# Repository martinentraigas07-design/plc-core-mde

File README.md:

# plc-core-mde
Open modular PLC based on ESP32 with web interface, IEC61131 FBD programming, RS485 Modbus expansion and cloud simulator support
# PLC-CORE-MDE

PLC-CORE-MDE is an open, modular and scalable programmable logic controller (PLC) based on ESP32, designed for education, automation, industrial control and experimental development.

The project is focused on creating a flexible, low-cost and high-performance control platform that can be expanded using external modules connected through RS485 Modbus communication.

The system includes an embedded web server that allows configuration, monitoring and programming directly from a web browser without the need for additional software.

Main features:

- ESP32 based core module
- Embedded web server
- Graphical programming using FBD (Function Block Diagram)
- IEC 61131 inspired runtime
- RS485 Modbus expansion modules
- Automatic module detection
- Digital and analog IO support
- PWM outputs
- Timers, counters and memory blocks
- Modular hardware for DIN rail mounting
- Educational oriented design
- Open architecture
- Cloud simulator support (future)
- Virtual PLC for training and testing

Architecture:

CORE module:
- Processing
- Web server
- Runtime
- Communication

Expansion modules:
- Digital inputs
- Digital outputs
- Analog inputs
- Analog outputs
- Mixed IO
- Modbus devices

Future features:

- Cloud PLC simulator
- USB communication mode
- Modbus remote mode
- Gateway mode
- Ethernet / TCP mode
- Hybrid simulation + real PLC

This project is intended for:

- Technical education
- Industrial automation learning
- Experimental development
- Custom control systems
- Low-cost PLC applications

Author: Martin Entraigas
Project: PLC-CORE-MDE

## License

PLC-CORE-MDE License v1.0

Copyright (c) 2026 Martín Entraigas / PLC-CORE-MDE, Argentina

Educational use allowed.
Commercial use requires authorization.

See LICENSE file for full terms.

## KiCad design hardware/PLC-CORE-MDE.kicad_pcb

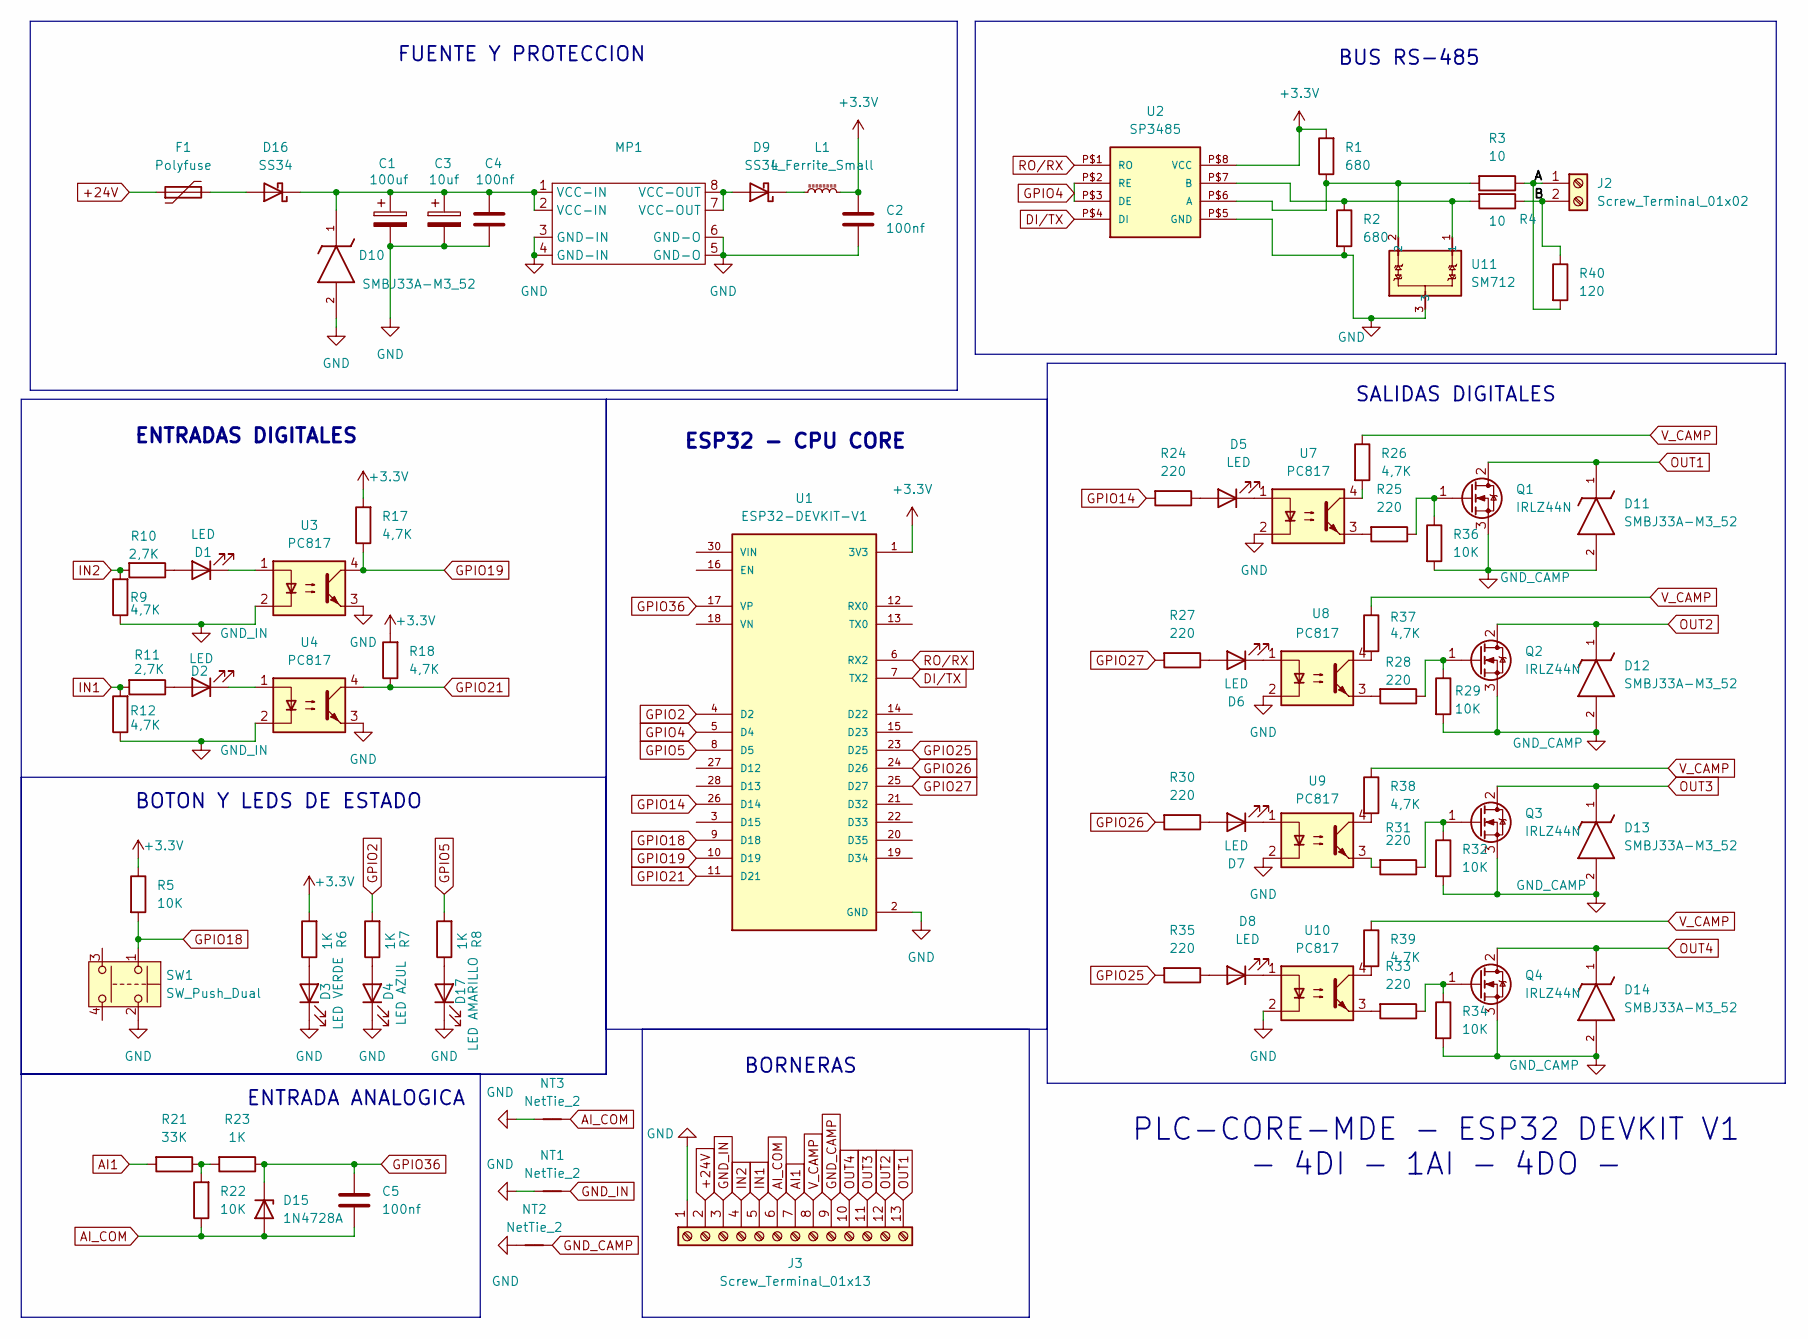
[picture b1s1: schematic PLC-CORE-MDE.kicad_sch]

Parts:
C1: 100uf; CP_Radial_D10.0mm_P2.50mm
C2, C4, C5: 100nf; C_Disc_D3.8mm_W2.6mm_P2.50mm
C3: 10uf; CP_Radial_D6.3mm_P2.50mm
D1, D2, D5, D6, D7, D8: LED; LED_D3.0mm
D3: LED VERDE; LED_D3.0mm
D4: LED AZUL; LED_D3.0mm
D9, D16: SS34; D_SMA
D10, D11, D12, D13, D14: SMBJ33A-M3_52; DIOM5436X244N; MANUFACTURER_PART_NUMBER SMBJ33A-M3/52
D15: 1N4728A; D_DO-34_SOD68_P2.54mm_Vertical_KathodeUp
D17: LED AMARILLO; LED_D3.0mm
F1: Polyfuse; C_Disc_D4.7mm_W2.5mm_P5.00mm
J2: Screw_Terminal_01x02; TerminalBlock_Phoenix_MKDS-3-2-5.08_1x02_P5.08mm_Horizontal
J3: Screw_Terminal_01x13; TerminalBlock_Phoenix_MKDS-3-13-5.08_1x13_P5.08mm_Horizontal
L1: L_Ferrite_Small; L_0805_2012Metric_Pad1.15x1.40mm_HandSolder
MP1: MP1584
NT1, NT2, NT3: NetTie_2; NetTie-2_SMD_Pad2.0mm
Q1, Q2, Q3, Q4: IRLZ44N; TO-220-3_Vertical
R1, R2: 680; R_Axial_DIN0204_L3.6mm_D1.6mm_P2.54mm_Vertical
R3, R4: 10; R_Axial_DIN0204_L3.6mm_D1.6mm_P2.54mm_Vertical
R5, R22, R29, R32, R34, R36: 10K; R_Axial_DIN0204_L3.6mm_D1.6mm_P2.54mm_Vertical
R6, R7, R8, R23: 1K; R_Axial_DIN0204_L3.6mm_D1.6mm_P2.54mm_Vertical
R9, R12, R17, R18, R26, R37, R38, R39: 4,7K; R_Axial_DIN0204_L3.6mm_D1.6mm_P2.54mm_Vertical
R10, R11: 2,7K; R_Axial_DIN0204_L3.6mm_D1.6mm_P2.54mm_Vertical
R21: 33K; R_Axial_DIN0204_L3.6mm_D1.6mm_P2.54mm_Vertical
R24, R25, R27, R28, R30, R31, R33, R35: 220; R_Axial_DIN0204_L3.6mm_D1.6mm_P2.54mm_Vertical
R40: 120; R_Axial_DIN0204_L3.6mm_D1.6mm_P2.54mm_Vertical
SW1: SW_Push_Dual; SW_PUSH_6mm
U1: ESP32-DEVKIT-V1; MODULE_ESP32_DEVKIT_V1; PARTREV N/A
U2: SP3485; SP3485-PAK
U3, U4, U7, U8, U9, U10: PC817; DIP-4_W7.62mm
U11: SM712; SOT23-WIDE

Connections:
+3.3V: C2.1, L1.2, R1.2, R5.1, R6.2, R17.2, R18.2, U1.1 (3V3), U2.P$8 (VCC)
+24V: F1.1, J3.2
AI1: J3.7, R21.2
AI_COM: C5.2, D15.2 (A), J3.6, NT3.2, R22.1
DI/TX: U1.7 (TX2), U2.P$4 (DI)
GND: C1.2, C2.2, C3.2, C4.2, D3.1 (K), D4.1 (K), D10.2, D17.1 (K), J3.1, MP1.3 (GND-IN), MP1.4 (GND-IN), MP1.5 (GND-O), MP1.6 (GND-O), NT1.1, NT2.1, NT3.1, R2.2, SW1.2, U1.2 (GND), U1.29 (GND), U2.P$5 (GND), U3.3, U4.3, U7.2, U8.2, U9.2, U10.2, U11.3
GND_CAMP: D11.2, D12.2, D13.2, D14.2, J3.9, NT2.2, Q1.3 (S), Q2.3 (S), Q3.3 (S), Q4.3 (S), R29.2, R32.2, R34.2, R36.2
GND_IN: J3.3, NT1.2, R9.1, R12.1, U3.2, U4.2
GPIO2: R7.2, U1.4 (D2)
GPIO4: U1.5 (D4), U2.P$2 (RE), U2.P$3 (DE)
GPIO5: R8.2, U1.8 (D5)
GPIO14: R24.2, U1.26 (D14)
GPIO18: R5.2, SW1.1, U1.9 (D18)
GPIO19: R17.1, U1.10 (D19), U3.4
GPIO21: R18.1, U1.11 (D21), U4.4
GPIO25: R35.2, U1.23 (D25)
GPIO26: R30.2, U1.24 (D26)
GPIO27: R27.2, U1.25 (D27)
GPIO36: C5.1, D15.1 (K), R23.1, U1.17 (VP)
IN1: J3.5, R11.2, R12.2
IN2: J3.4, R9.2, R10.2
unnamed: D1.2 (A), R10.1
unnamed: D1.1 (K), U3.1
unnamed: D2.2 (A), R11.1
unnamed: D2.1 (K), U4.1
unnamed: D3.2 (A), R6.1
unnamed: D4.2 (A), R7.1
unnamed: D5.2 (A), R24.1
unnamed: D5.1 (K), U7.1
unnamed: D6.2 (A), R27.1
unnamed: D6.1 (K), U8.1
unnamed: D7.2 (A), R30.1
unnamed: D7.1 (K), U9.1
unnamed: D8.2 (A), R35.1
unnamed: D8.1 (K), U10.1
unnamed: D9.2 (A), MP1.7 (VCC-OUT), MP1.8 (VCC-OUT)
unnamed: D9.1 (K), L1.1
unnamed: D16.2 (A), F1.2
unnamed: C1.1, C3.1, C4.1, D10.1, D16.1 (K), MP1.1 (VCC-IN), MP1.2 (VCC-IN)
unnamed: D17.2 (A), R8.1
unnamed: Q1.1 (G), R25.1, R36.1
unnamed: Q2.1 (G), R28.1, R29.1
unnamed: Q3.1 (G), R31.1, R32.1
unnamed: Q4.1 (G), R33.1, R34.1
unnamed: R21.1, R22.2, R23.2
unnamed: R25.2, U7.3
unnamed: R26.2, U7.4
unnamed: R28.2, U8.3
unnamed: R31.2, U9.3
unnamed: R33.2, U10.3
unnamed: R37.2, U8.4
unnamed: R38.2, U9.4
unnamed: R39.2, U10.4
unnamed: R1.1, R3.2, U2.P$6 (A), U11.2
unnamed: R2.1, R4.2, U2.P$7 (B), U11.1
OUT1: D11.1, J3.13, Q1.2 (D)
OUT2: D12.1, J3.12, Q2.2 (D)
OUT3: D13.1, J3.11, Q3.2 (D)
OUT4: D14.1, J3.10, Q4.2 (D)
RO/RX: U1.6 (RX2), U2.P$1 (RO)
V_CAMP: J3.8, R26.1, R37.1, R38.1, R39.1

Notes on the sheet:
SALIDAS DIGITALES
ENTRADA ANALOGICA
PLC-CORE-MDE - ESP32 DEVKIT V1 - 4DI - 1AI - 4DO -
BOTON Y LEDS DE ESTADO
BUS RS-485
BORNERAS
ENTRADAS DIGITALES
ESP32 - CPU CORE
FUENTE Y PROTECCION

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
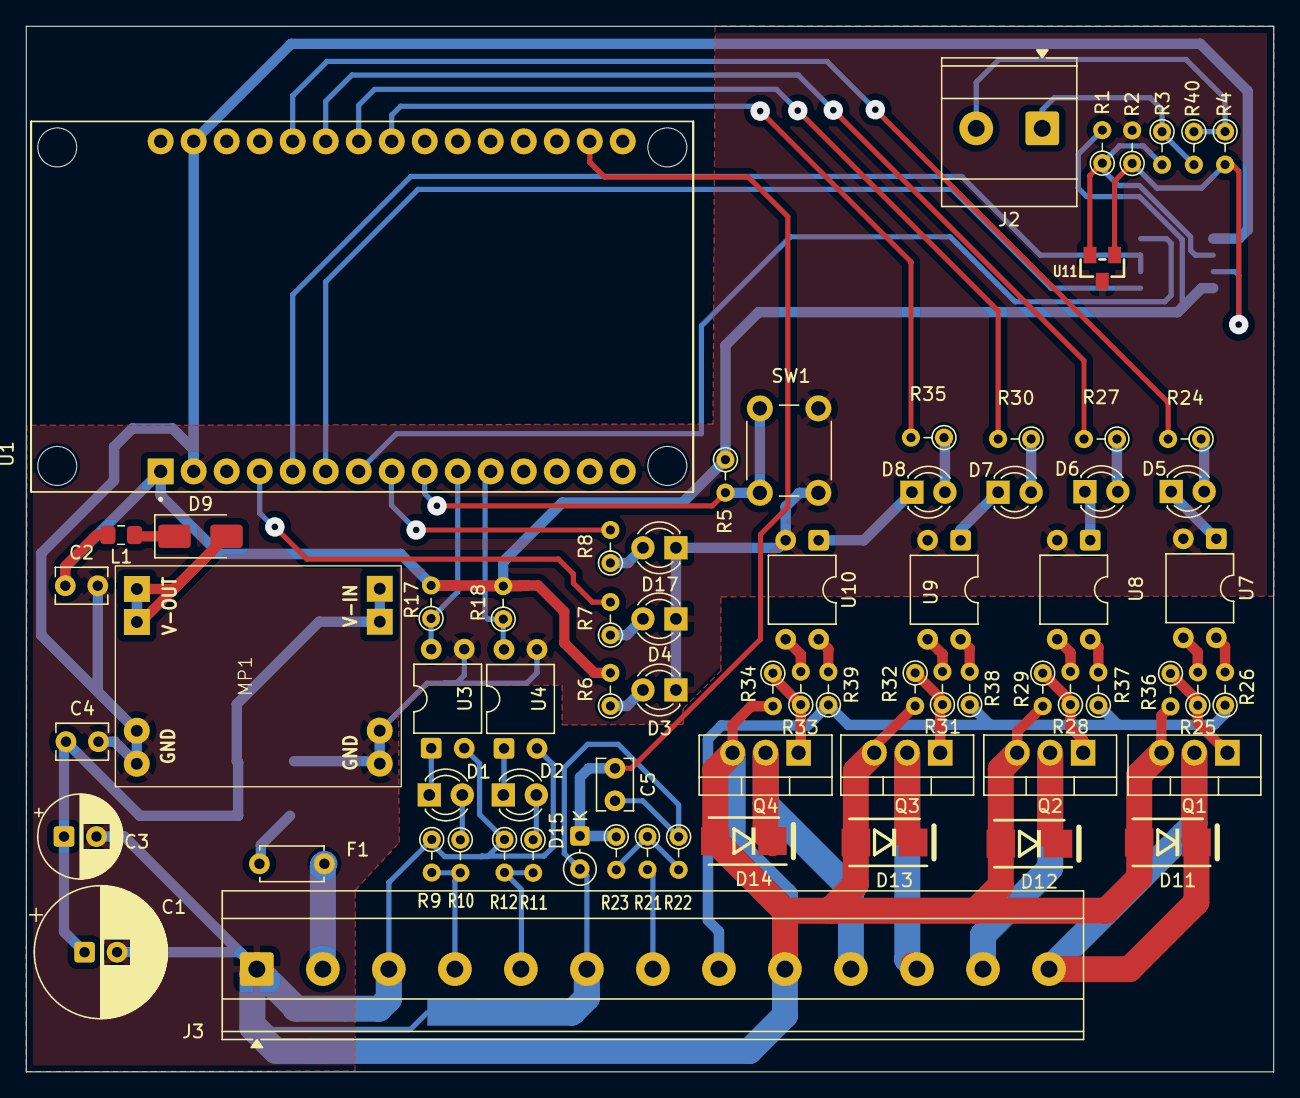
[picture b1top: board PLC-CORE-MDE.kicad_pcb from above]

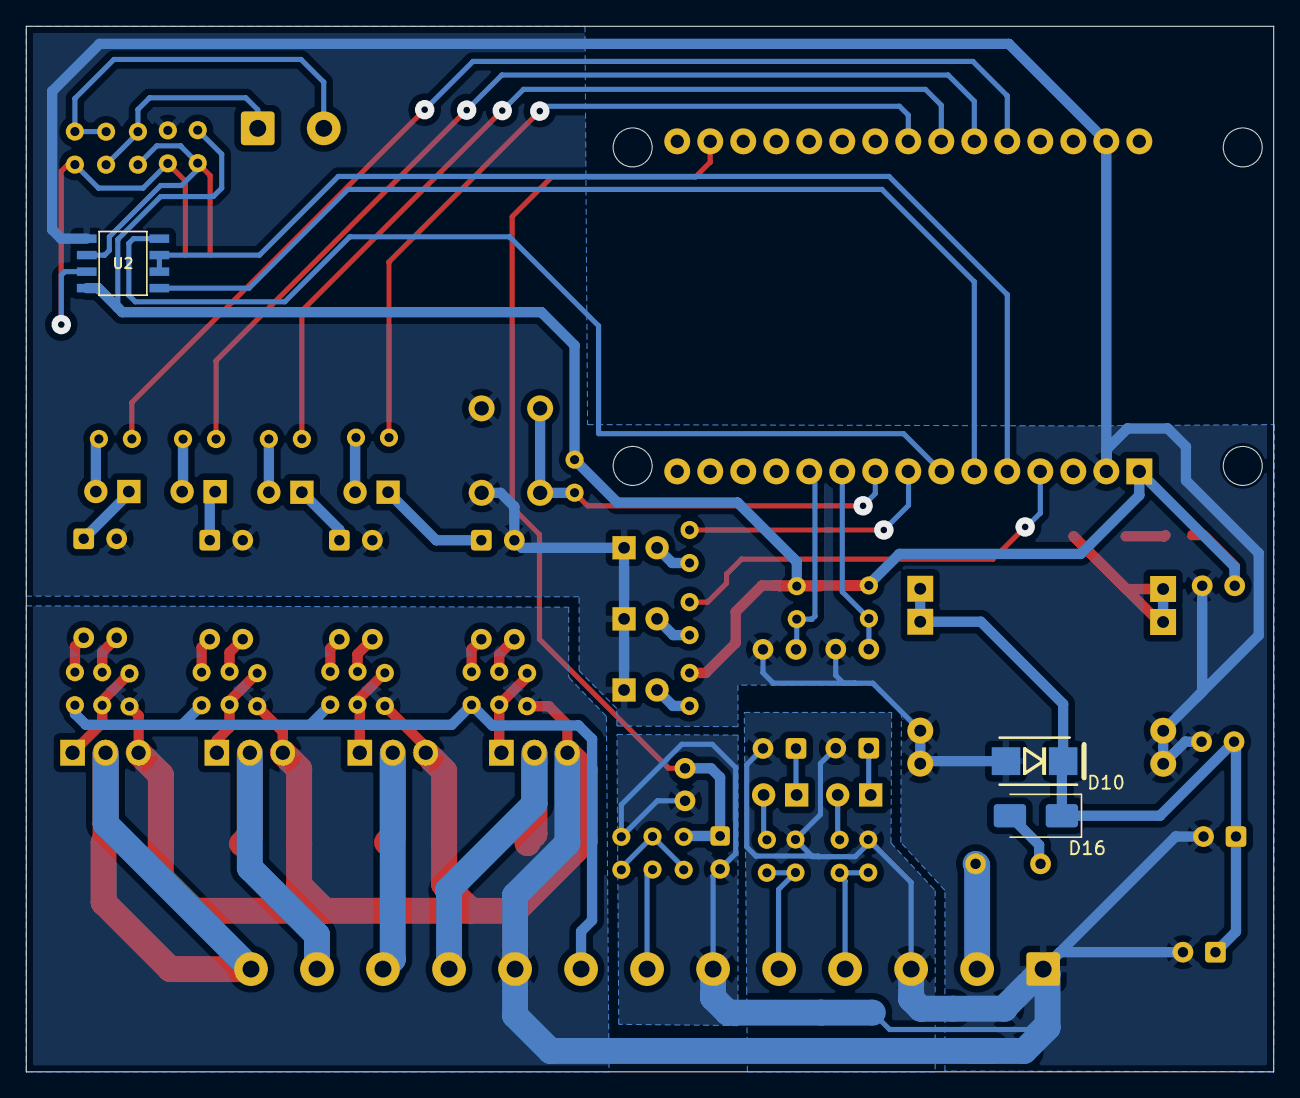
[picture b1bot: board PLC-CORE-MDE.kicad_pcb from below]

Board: 2 copper layers, 96.0 x 80.5 mm, 78 parts (6 on the bottom side), 63 nets.

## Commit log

2026-03-26 README.md
2026-03-26 Add files via upload
    Add web server + simulator
2026-03-27 Create LICENSE
2026-03-27 Create NOTICE
